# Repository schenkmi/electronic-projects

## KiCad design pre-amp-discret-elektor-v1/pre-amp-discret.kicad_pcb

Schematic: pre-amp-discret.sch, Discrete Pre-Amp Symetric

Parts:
C1, C3, C15, C16, C18, C19: 220uF; CP_Radial_D8.0mm_P3.50mm
C2: 3.3uF; C_Rect_L7.2mm_W7.2mm_P5.00mm_FKS2_FKP2_MKS2_MKP2
C4, C5, C13, C14: 100nF; C_Rect_L7.2mm_W2.5mm_P5.00mm_FKS2_FKP2_MKS2_MKP2
C6: 100uF; CP_Radial_D5.0mm_P2.00mm
C7, C8: 150p; C_0805_2012Metric_Pad1.18x1.45mm_HandSolder
C9: 1uF; C_Rect_L7.2mm_W5.5mm_P5.00mm_FKS2_FKP2_MKS2_MKP2
C10, C20: 2.2uF; C_1210_3225Metric_Pad1.33x2.70mm_HandSolder
C11, C17: 100nF; C_0805_2012Metric_Pad1.18x1.45mm_HandSolder
C12: 6.8pF; C_0805_2012Metric_Pad1.18x1.45mm_HandSolder
C21: 33p; C_0805_2012Metric_Pad1.18x1.45mm_HandSolder
D1, D2: 1N4148W; D_SOD-123
H1, H2, H3, H4: MountingHole; MountingHole_3.2mm_M3
J1, J2, J3, J4, J5, J6, J7: Conn_01x01; Pin_D1.0mm_L10.0mm
Q1, Q3: BCM857DS,115; SC-74-6_1.5x2.9mm_P0.95mm
Q2, Q9: BC850C; SOT-23
Q4: BC550C; TO-92_Inline
Q5: BC560C; TO-92_Inline
Q6: BC337-40; TO-92_Inline
Q7: BC860C; SOT-23
Q8: BC327-40; TO-92_Inline
Q11, Q13: BCM847DS,115; SC-74-6_1.5x2.9mm_P0.95mm
R1, R7, R8, R9, R10, R12, R25: 10k; R_0805_2012Metric_Pad1.20x1.40mm_HandSolder
R2, R5, R21, R24: 80.6R; R_0805_2012Metric_Pad1.20x1.40mm_HandSolder
R3, R6, R20, R23: 806R; R_0805_2012Metric_Pad1.20x1.40mm_HandSolder
R4, R22: 140R; R_0805_2012Metric_Pad1.20x1.40mm_HandSolder
R11, R27: 249R; R_0805_2012Metric_Pad1.20x1.40mm_HandSolder
R13: 47R; R_0805_2012Metric_Pad1.20x1.40mm_HandSolder
R14, R15: 390R; R_0805_2012Metric_Pad1.20x1.40mm_HandSolder
R16, R17: 10R; R_0805_2012Metric_Pad1.20x1.40mm_HandSolder
R18, R26: 392k; R_0805_2012Metric_Pad1.20x1.40mm_HandSolder
R19: 100k; R_0805_2012Metric_Pad1.20x1.40mm_HandSolder
R28: 3.9k; R_0805_2012Metric_Pad1.20x1.40mm_HandSolder
R29: 27k; R_0805_2012Metric_Pad1.20x1.40mm_HandSolder
R30, R31: 475k; R_0805_2012Metric_Pad1.20x1.40mm_HandSolder
R32: 470R; R_0805_2012Metric_Pad1.20x1.40mm_HandSolder
RV1: 10k; Potentiometer_Bourns_3266W_Vertical
RV2: 100k; Potentiometer_Bourns_3266W_Vertical
U1: OPA188xxDBV; TSOT-23-5

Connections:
+15V: C1.1, C4.2, C11.2, C13.2, C15.1, C18.1, J1.1, Q3.4 (E2), Q6.1 (C), R4.1, R11.1, R20.1, R23.1, U1.5
-15V: C3.2, C5.1, C14.1, C16.2, C17.2, C19.2, J3.1, Q8.1 (C), Q11.4 (E2), R3.2, R6.2, R22.2, R27.2, R28.2, RV2.1, RV2.2, U1.2
GND: C1.2, C3.1, C4.1, C5.2, C6.2, C7.1, C8.2, C11.1, C13.1, C14.2, C15.2, C16.1, C17.1, C18.2, C19.1, C20.1, C21.1, D1.1 (K), D2.2 (A), J2.1, J5.1, J7.1, R1.2, R7.2, R25.1, R30.2
unnamed: C2.1, R32.2
unnamed: C2.2, J4.1
unnamed: C6.1, R8.2
unnamed: C7.2, R10.2
unnamed: C8.1, R12.1
unnamed: C9.1, Q2.3 (C), Q5.1 (C), Q8.2 (B), R12.2, R15.2
unnamed: C9.2, Q4.1 (C), Q6.2 (B), Q7.3 (C), R10.1, R14.1
unnamed: C10.1, R29.1, U1.1
unnamed: C10.2, R30.1, U1.4
unnamed: C12.1, R9.1, R13.2, R16.2, R17.1, R31.1
unnamed: C12.2, Q1.5 (B2), Q13.5 (B2), R8.1, R9.2, R26.1
unnamed: C20.2, D1.2 (A), D2.1 (K), R31.2, U1.3
unnamed: C21.2, Q1.2 (B1), Q13.2 (B1), R1.1, R18.1, R32.1
unnamed: J6.1, R13.1
unnamed: Q1.1 (E1), R2.2
unnamed: Q1.3 (C2), R6.1
unnamed: Q1.4 (E2), R5.2
unnamed: Q1.6 (C1), Q2.1 (B), R3.1
unnamed: Q2.2 (E), R27.1
unnamed: Q3.1 (E1), Q3.5 (B2), R4.2
unnamed: Q3.2 (B1), Q3.3 (C2), R7.1
unnamed: Q3.6 (C1), R2.1, R5.1
unnamed: Q4.2 (B), R14.2, RV1.1
unnamed: Q4.3 (E), Q5.3 (E)
unnamed: Q5.2 (B), R15.1, RV1.2, RV1.3
unnamed: Q6.3 (E), R16.1
unnamed: Q7.2 (E), R11.2
unnamed: Q8.3 (E), R17.2
unnamed: Q9.1 (B), R28.1, R29.2
unnamed: Q9.2 (E), R19.1
unnamed: Q9.3 (C), R18.2, R26.2
unnamed: Q11.1 (E1), Q11.5 (B2), R22.1
unnamed: Q11.2 (B1), Q11.3 (C2), R25.2
unnamed: Q11.6 (C1), R21.2, R24.2
unnamed: Q13.1 (E1), R21.1
unnamed: Q13.3 (C2), R23.2
unnamed: Q13.4 (E2), R24.1
unnamed: Q7.1 (B), Q13.6 (C1), R20.2
unnamed: R19.2, RV2.3

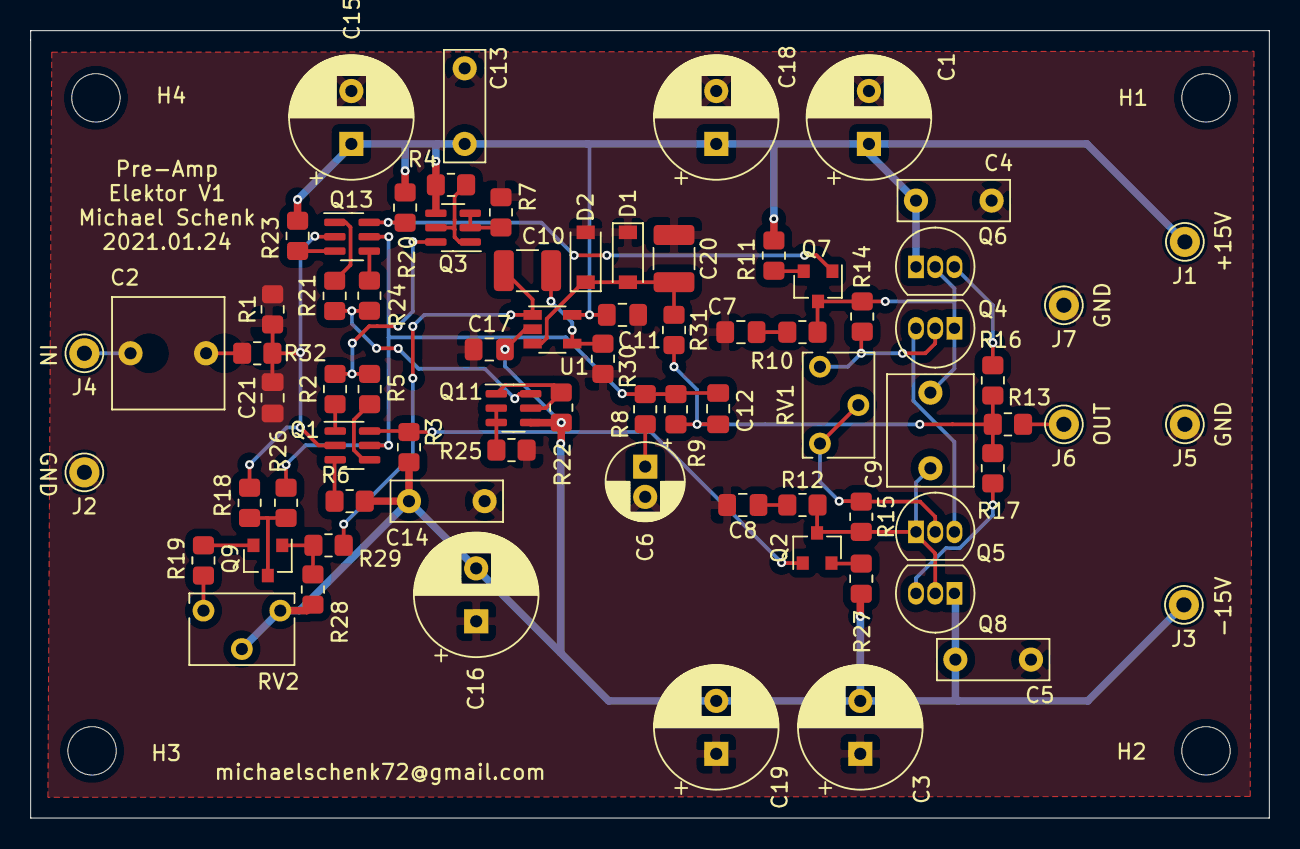
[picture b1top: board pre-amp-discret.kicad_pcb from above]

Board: 2 copper layers, 81.9 x 52.1 mm, 80 parts (0 on the bottom side), 42 nets.
